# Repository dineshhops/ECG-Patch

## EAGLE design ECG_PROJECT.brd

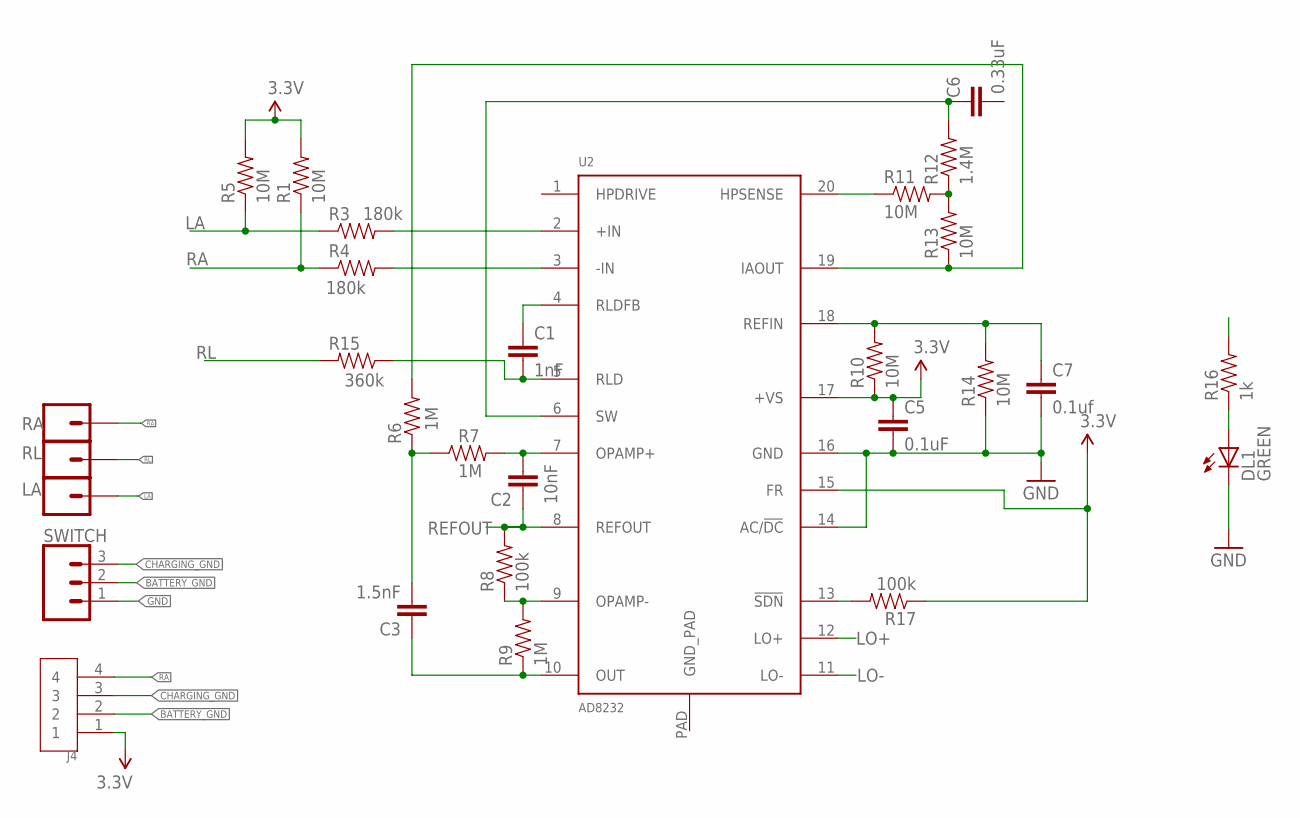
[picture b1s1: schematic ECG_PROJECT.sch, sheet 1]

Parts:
C1: 1nF; 0603-CAP
C2: 10nF; 0603-CAP
C3: 1.5nF; 0603-CAP
C5: 0.1uF; 0603-CAP
C6: 0.33uF; 0603-CAP
C7: 0.1uf; 0603-CAP
DL1: GREEN; LEDC1608X80N-AK
J4: CON-FPC-1MM-04-TE$20$CONNECTIVITY$20$AMP$20$CONNE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; FPC-4PIN
LA: CONN_01; 1X01
R1, R5, R10, R11, R13, R14: 10M; 0603-RES
R3, R4: 180k; 0603-RES
R6, R7, R9: 1M; 0603-RES
R8, R17: 100k; 0603-RES
R12: 1.4M; 0603-RES
R15: 360k; 0603-RES
R16: 1k; 0603-RES
RA: CONN_01; 1X01
RL: CONN_01; 1X01
SWITCH: 455-1750-1-ND; 1X03
U2: AD8232; LFCSP_20

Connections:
3.3V: C5.1, J4.1, R1.2, R5.2, R10.1, R17.1, U2.15 (FR), U2.17 (+VS); also elsewhere on the board
AIN3_A0: C3.1, R9.1, R16.2, U2.10 (OUT); also elsewhere on the board
BATTERY_GND: J4.2, SWITCH.2
CHARGING_GND: J4.3, SWITCH.3
GND: C5.2, C7.2, DL1.C, R14.1, SWITCH.1, U2.14 (AC/!DC), U2.16 (GND); also elsewhere on the board
LA: LA.1, R3.1, R5.1
LO+: U2.12 (LO+); also elsewhere on the board
LO-: U2.11 (LO-); also elsewhere on the board
unnamed: R3.2, U2.2 (+IN)
unnamed: R4.2, U2.3 (-IN)
unnamed: C2.2, R7.2, U2.7 (OPAMP+)
unnamed: R11.1, U2.20 (HPSENSE)
unnamed: C7.1, R10.2, R14.2, U2.18 (REFIN)
unnamed: R8.1, R9.2, U2.9 (OPAMP-)
unnamed: R6.2, R13.1, U2.19 (IAOUT)
unnamed: C3.2, R6.1, R7.1
unnamed: R17.2, U2.13 (!SDN)
unnamed: DL1.A, R16.1
unnamed: R11.2, R12.1, R13.2
unnamed: C6.1, R12.2, U2.6 (SW)
unnamed: C1.1, U2.4 (RLDFB)
unnamed: C1.2, R15.1, U2.5 (RLD)
RA: J4.4, R1.1, R4.1, RA.1
REFOUT: C2.1, R8.2, U2.8 (REFOUT)
RL: R15.2, RL.1

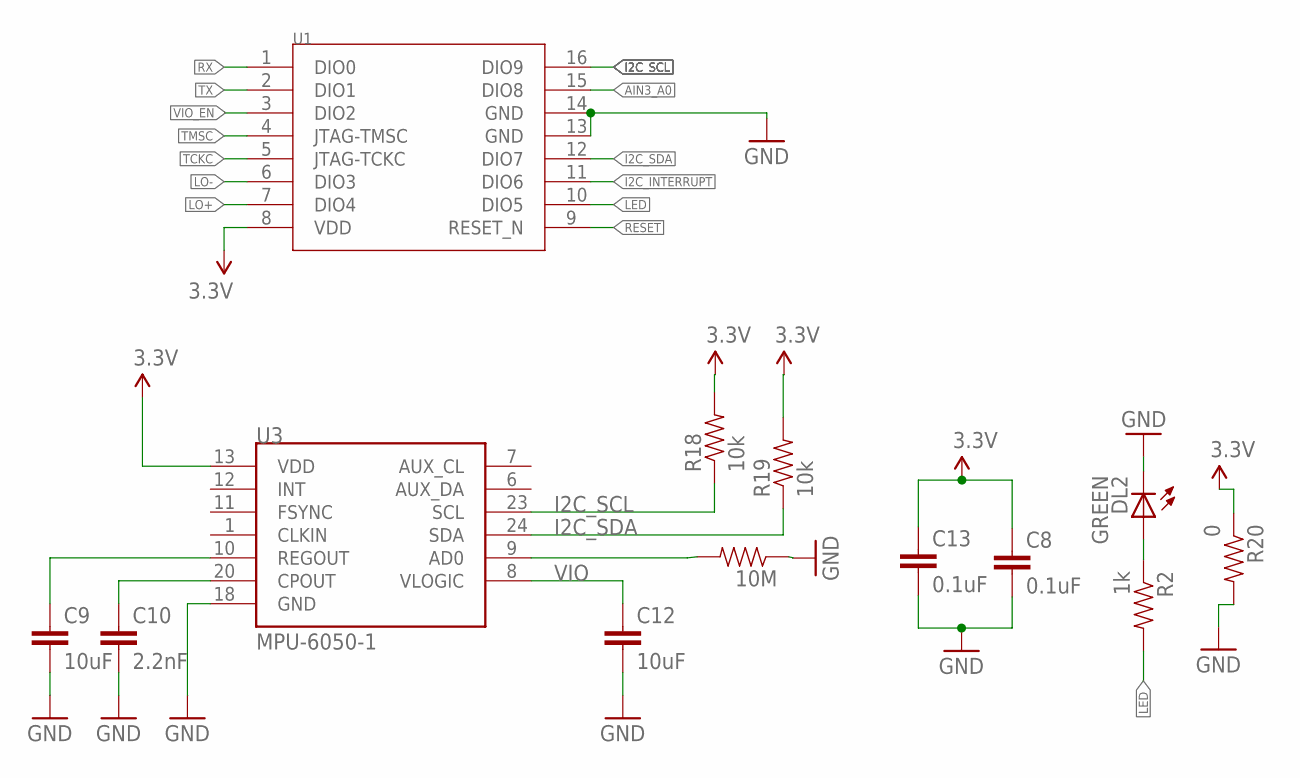
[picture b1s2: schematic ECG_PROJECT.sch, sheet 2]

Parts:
10M: 1k; 0603-RES
C8, C13: 0.1uF; 0603-CAP
C9, C12: 10uF; 0603-CAP
C10: 2.2nF; 0603-CAP
DL2: GREEN; LEDC1608X80N-AK
R2: 1k; 0603-RES
R18, R19: 10k; 0603-RES
R20: 0; 0603-RES
U1: IC-MCU-5.1GHZ-CANSECIC-MCU-5.1GHZ-CANSEC_AN2640R2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; AN2640R2SA-K_MODULE$20$-$20$DUPLICATE
U3: MPU-6050-1; QFN-24-4MM2

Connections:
3.3V: C8.1, C13.1, R18.2, R19.2, R20.1, U1.8 (VDD), U3.13 (VDD); also elsewhere on the board
AIN3_A0: U1.15 (DIO8); also elsewhere on the board
GND: 10M.1, C8.2, C9.2, C10.2, C12.2, C13.2, DL2.C, R20.2, U1.13 (GND), U1.14 (GND), U3.18 (GND); also elsewhere on the board
I2C_INTERRUPT: U1.11 (DIO6)
I2C_SCL: R18.1, U1.16 (DIO9), U3.23 (SCL)
I2C_SDA: R19.1, U1.12 (DIO7), U3.24 (SDA)
LED: R2.2, U1.10 (DIO5)
LO+: U1.7 (DIO4); also elsewhere on the board
LO-: U1.6 (DIO3); also elsewhere on the board
unnamed: DL2.A, R2.1
unnamed: C10.1, U3.20 (CPOUT)
unnamed: C9.1, U3.10 (REGOUT)
unnamed: 10M.2, U3.9 (AD0)
RESET: U1.9 (RESET_N)
RX: U1.1 (DIO0)
TCKC: U1.5 (JTAG-TCKC)
TMSC: U1.4 (JTAG-TMSC)
TX: U1.2 (DIO1)
VIO: C12.1, U3.8 (VLOGIC)
VIO_EN: U1.3 (DIO2)

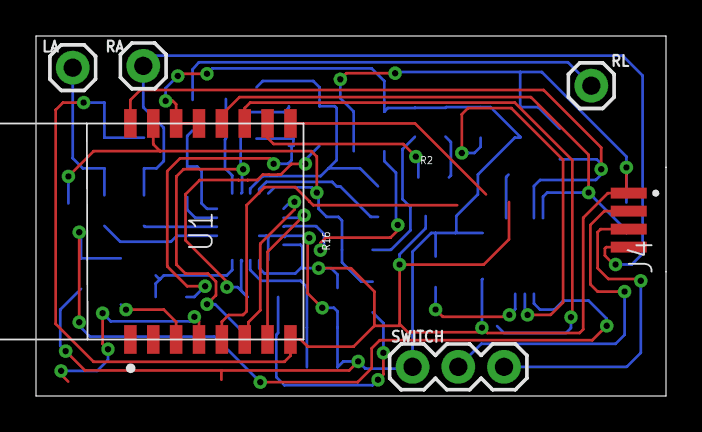
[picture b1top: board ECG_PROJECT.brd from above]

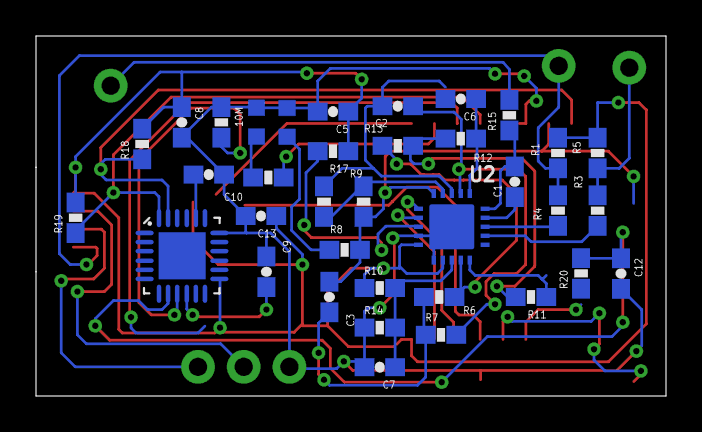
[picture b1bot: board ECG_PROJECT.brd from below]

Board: 2 copper layers, 35.0 x 20.0 mm, 42 parts (36 on the bottom side), 33 nets.

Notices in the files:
parts and their libraries:
SparkFun-Connectors: Licensing: CC v3.0 Share-Alike You are welcome to use this library for commercial purposes.
